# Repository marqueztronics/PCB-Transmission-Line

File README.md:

# PCB Transmission Line

A simple board with a 50-ohm transmission line for observing waves and reflections under the oscilloscope.

## Board Images

### Top View - 2D

### Bottom View - 2D

### Isometric

### Top View - 3D Render

### Bottom View - 3D

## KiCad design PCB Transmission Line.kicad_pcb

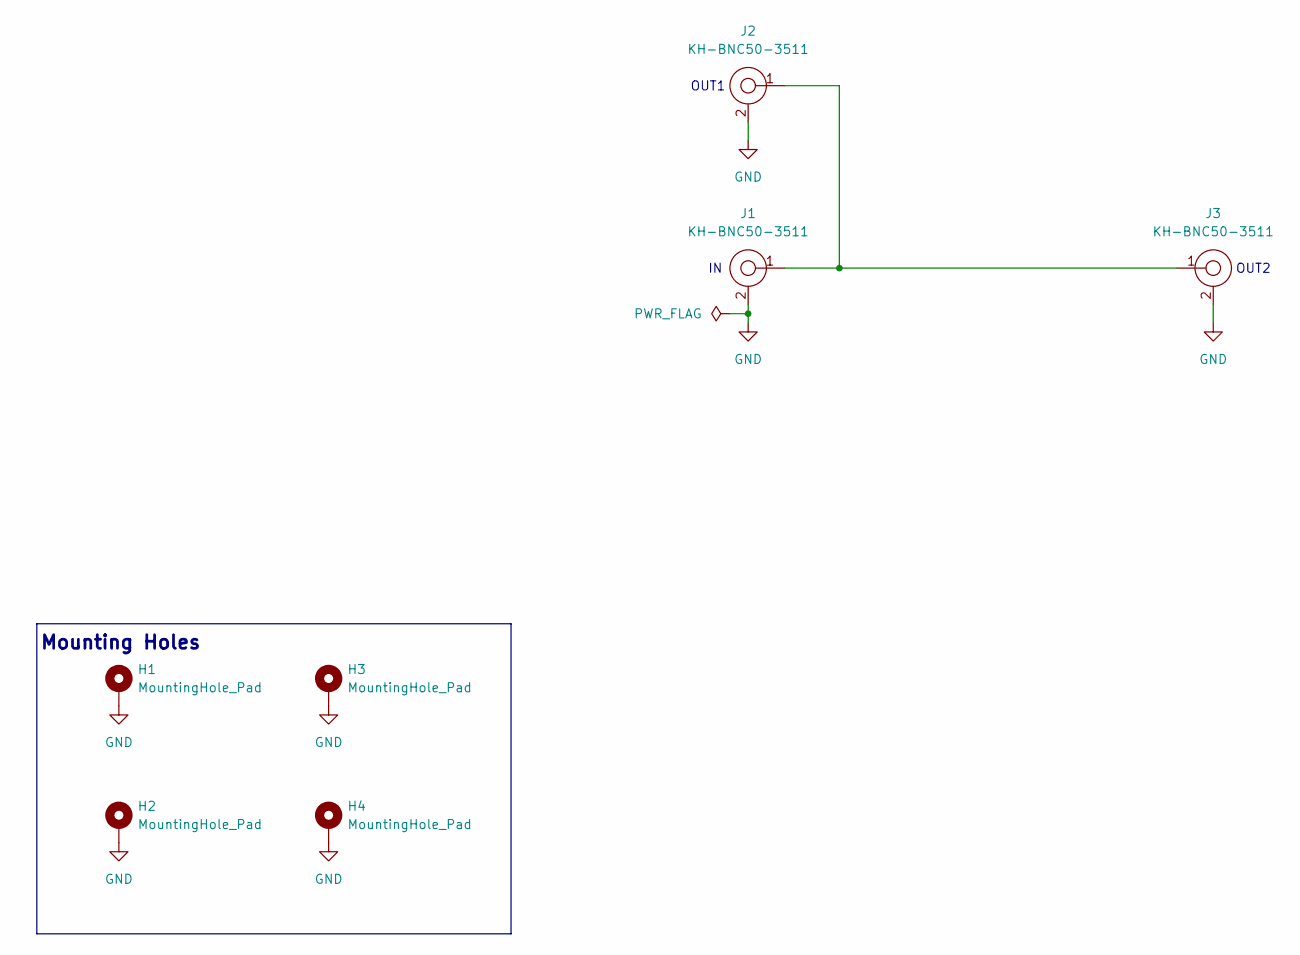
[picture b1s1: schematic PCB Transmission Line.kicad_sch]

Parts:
H1, H2, H3, H4: MountingHole_Pad; MountingHole_3.2mm_M3_Pad
J1, J2, J3: KH-BNC50-3511; CONN_BNC_THT_RA_KH-BNC50-3511; Manufacturer Part Number KH-BNC50-3511

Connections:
GND: H1.1, H2.1, H3.1, H4.1, J1.2, J2.2, J3.2
unnamed: J1.1, J2.1, J3.1

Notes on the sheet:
Mounting Holes
OUT1
OUT2

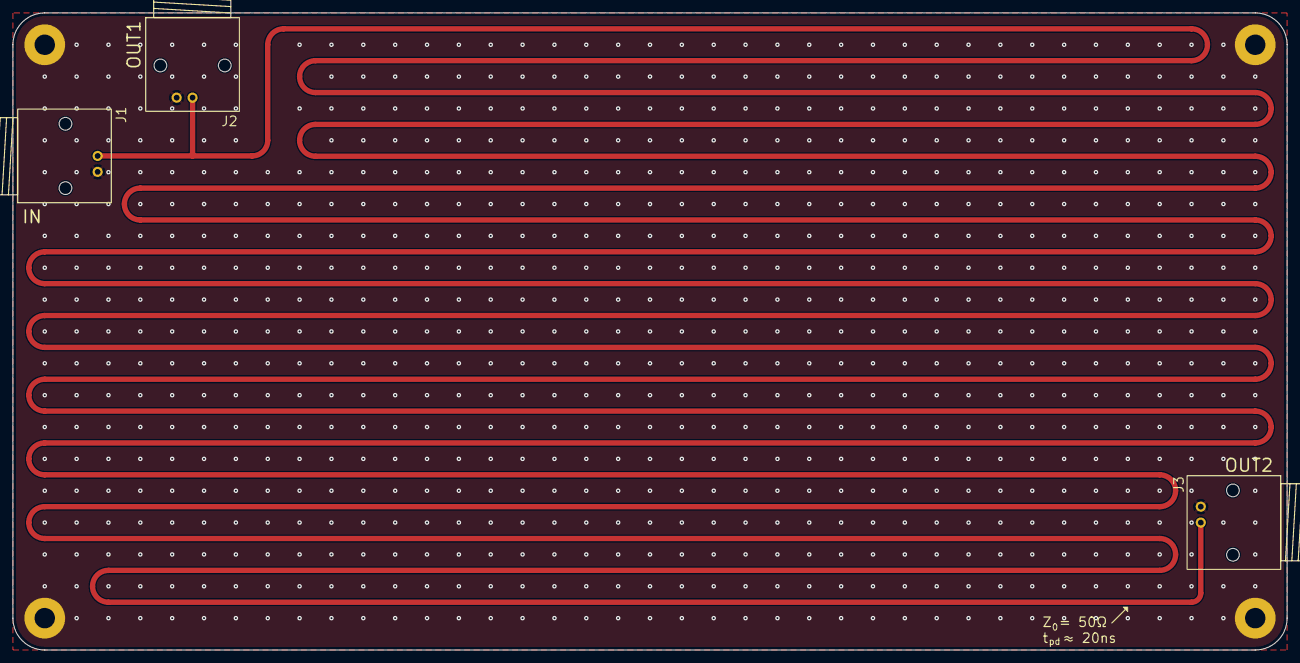
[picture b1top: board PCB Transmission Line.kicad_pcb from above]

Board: 2 copper layers, 200.0 x 100.0 mm, 7 parts (0 on the bottom side), 2 nets.

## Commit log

2025-08-16 Initial commit. Board fully routed
2025-08-17 Add silkscreen notes and equations
2025-08-22 Finish silkscreen notes and plot Gerber files
2025-08-22 Move BOM inside BOM directory
2025-08-26 Update BOM column structure
2025-08-26 Add Description column to BOM
2025-08-26 Update README.md
    Add PCB images.
2025-08-28 Add license and copyright notice to Schematic and PCB documents
2025-08-28 Add copyright notice to Schematic document that was missing

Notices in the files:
PCB Transmission Line.kicad_pcb:
CERN-OHL-P-2.0 license
© 2025 Leonardo Marquez
© Leonardo Márquez, 2025
